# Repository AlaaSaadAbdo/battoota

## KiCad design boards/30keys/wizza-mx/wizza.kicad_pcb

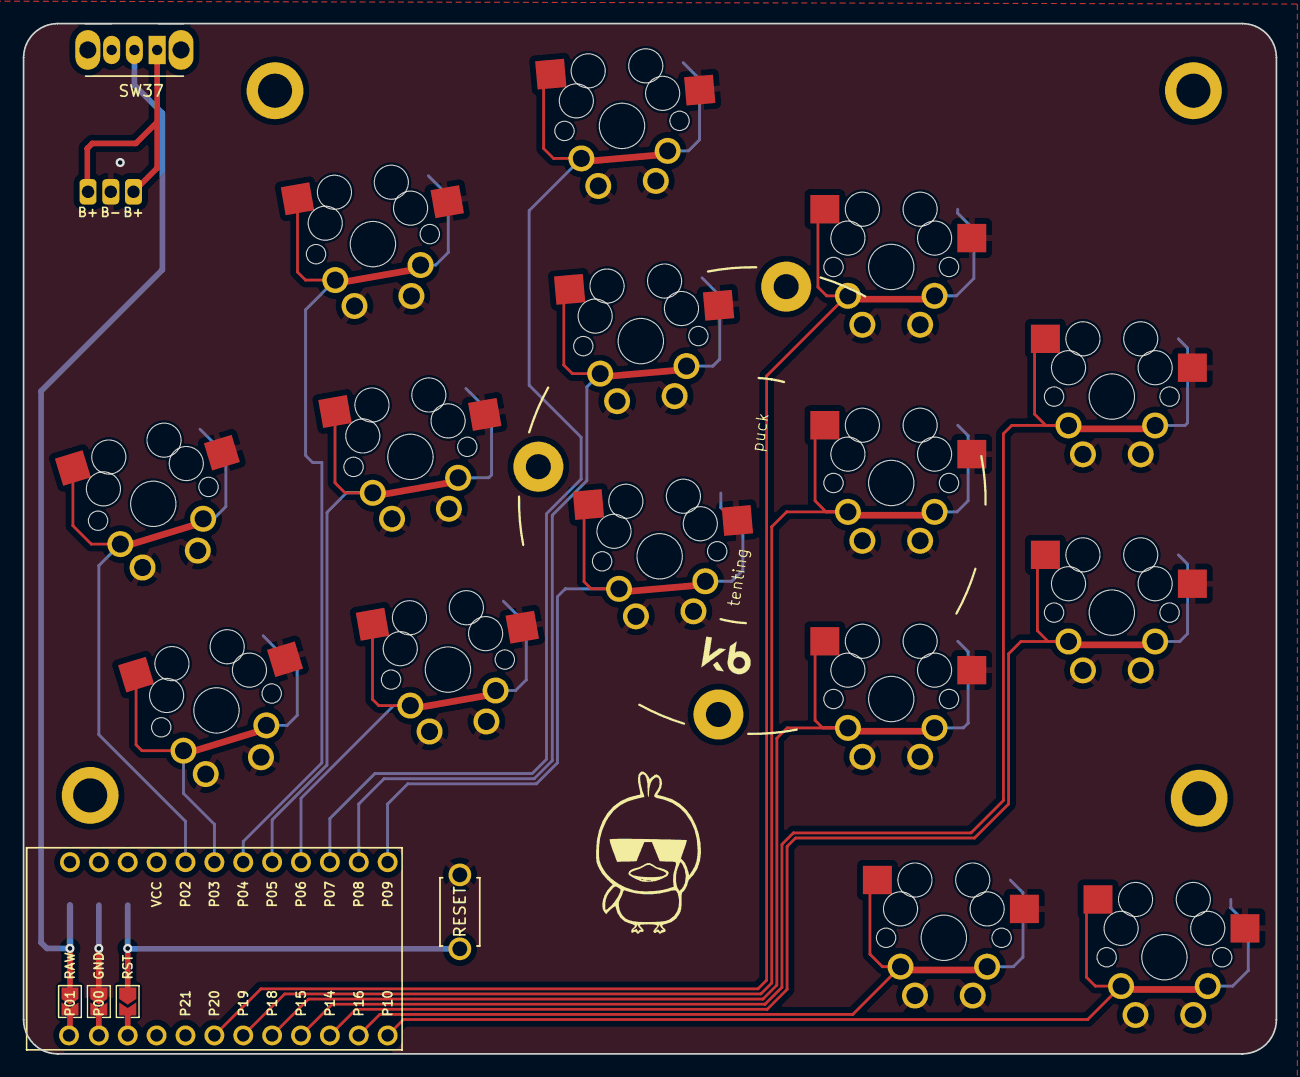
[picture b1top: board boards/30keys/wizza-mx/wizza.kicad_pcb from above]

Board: 2 copper layers, 110.2 x 90.6 mm, 19 parts (0 on the bottom side), 19 nets.

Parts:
B1: ResetSW
MCU1: ProMicro32keys
PAD1: bat
S1, S2, S3, S4, S5, S6, S7, S8, S9, S10, S11, S12, S13, S14, S15: MX-hotswap-reversible
SW37: SW_SPDT; SW_CuK_OS102011MA1QN1_SPDT_Angled

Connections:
GND: B1.2, MCU1.2, PAD1.2, S1.1, S2.1, S3.1, S4.1, S5.1, S6.1, S7.1, S8.1, S9.1, S10.1, S11.1, S12.1, S13.1, S14.1, S15.1
RAW: MCU1.1, SW37.2 (B)
RST: B1.1, MCU1.3
b+: PAD1.1, PAD1.3, SW37.1 (A)
matrix_index_bottom: MCU1.8, S9.2
matrix_index_home: MCU1.7, S10.2
matrix_index_top: MCU1.6, S11.2
matrix_inner_bottom: MCU1.10, S12.2
matrix_inner_home: MCU1.9, S13.2
matrix_middle_bottom: MCU1.24, S6.2
matrix_middle_home: MCU1.23, S7.2
matrix_middle_top: MCU1.22, S8.2
matrix_pinky_home: MCU1.18, S1.2
matrix_pinky_top: MCU1.17, S2.2
matrix_ring_bottom: MCU1.21, S3.2
matrix_ring_home: MCU1.20, S4.2
matrix_ring_top: MCU1.19, S5.2
thumb_reachy: MCU1.12, S15.2
thumb_tucky: MCU1.11, S14.2

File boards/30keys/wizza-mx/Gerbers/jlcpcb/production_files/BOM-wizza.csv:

Comment,Designator,Footprint,LCSC
,S7,MX-hotswap-reversible,
,S8,MX-hotswap-reversible,
,S4,MX-hotswap-reversible,
,MCU1,ProMicro32keys,
,S1,MX-hotswap-reversible,
,S9,MX-hotswap-reversible,
,S12,MX-hotswap-reversible,
,S14,MX-hotswap-reversible,
,S3,MX-hotswap-reversible,
,T2,SPDT_C128955,
,S6,MX-hotswap-reversible,
,S15,MX-hotswap-reversible,
,PAD1,bat,
,B1,ResetSW,
,S11,MX-hotswap-reversible,
,S2,MX-hotswap-reversible,
,S13,MX-hotswap-reversible,
,S5,MX-hotswap-reversible,
,S10,MX-hotswap-reversible,
,T1,SPDT_C128955,

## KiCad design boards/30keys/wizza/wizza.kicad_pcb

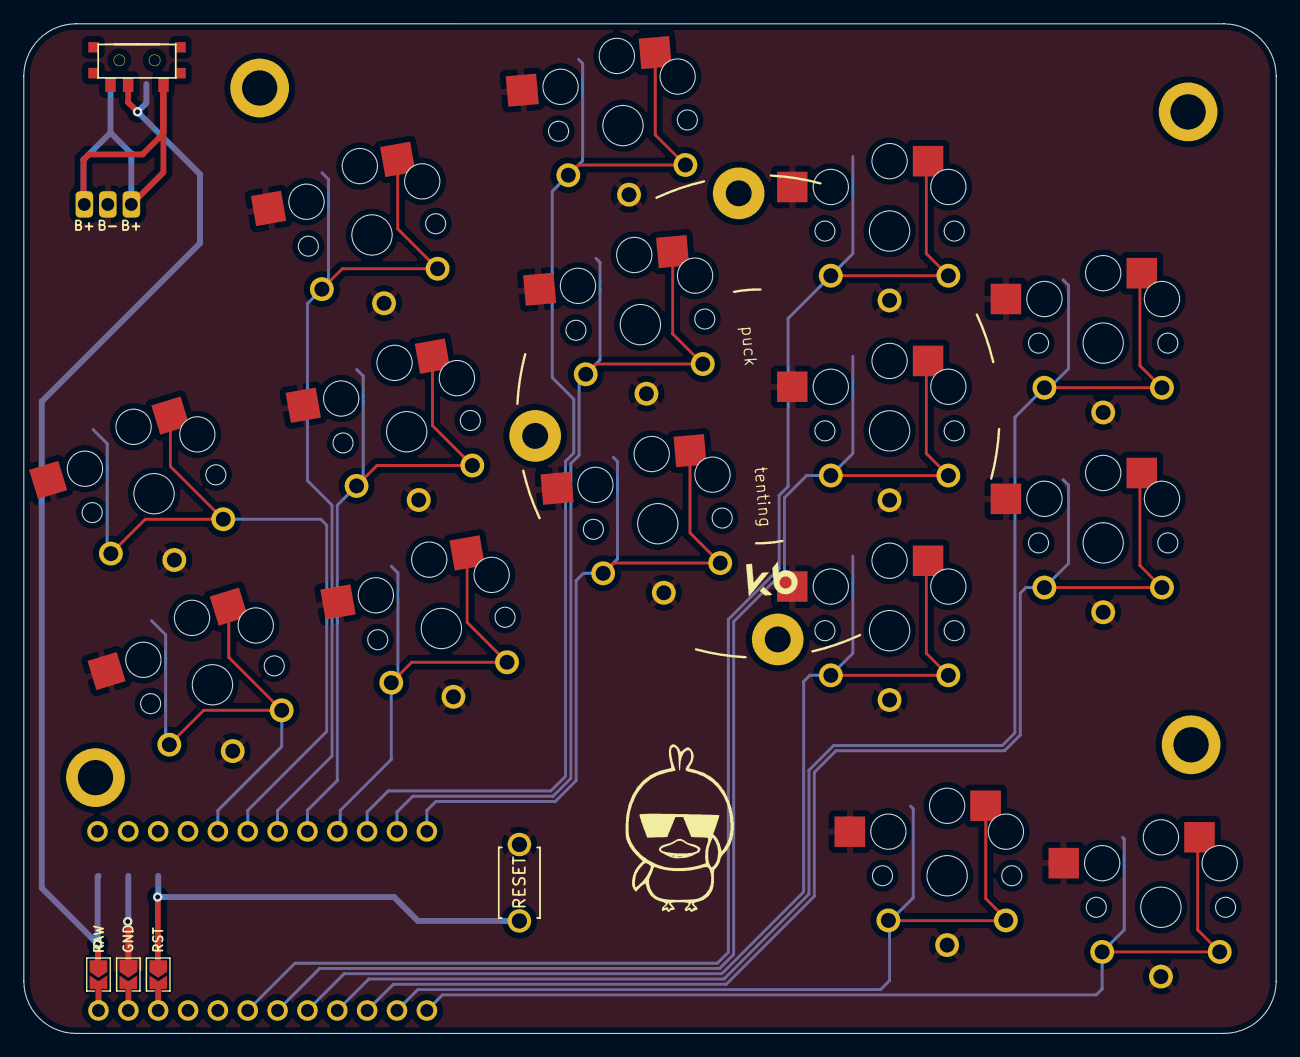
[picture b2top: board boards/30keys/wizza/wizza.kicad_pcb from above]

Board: 2 copper layers, 106.6 x 85.9 mm, 20 parts (1 on the bottom side), 19 nets.

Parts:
B1: ResetSW
MCU1: ProMicro
PAD1: bat
S3, S5, S7, S9, S11, S13, S15, S17, S19, S21, S23, S27, S29, S31, S33: choc_hotswap_key
T1, T2: SPDT_C128955

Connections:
Braw: PAD1.1, PAD1.3, T1.1, T2.1
GND: B1.2, MCU1.2, PAD1.2, S3.2, S5.2, S7.2, S9.2, S11.2, S13.2, S15.2, S17.2, S19.2, S21.2, S23.2, S27.2, S29.2, S31.2, S33.2
P3: MCU1.18, S23.1
P4: MCU1.19, S21.1
P5: MCU1.20, S19.1
P6: MCU1.21, S29.1
P7: MCU1.22, S27.1
P8: MCU1.23, S31.1
P9: MCU1.24, S33.1
P10: MCU1.12, S13.1
P14: MCU1.10, S17.1
P15: MCU1.9, S7.1
P16: MCU1.11, S15.1
P18: MCU1.8, S9.1
P19: MCU1.7, S11.1
P20: MCU1.6, S5.1
P21: MCU1.5, S3.1
RAW: MCU1.1, T1.2, T2.2
RST: B1.1, MCU1.3

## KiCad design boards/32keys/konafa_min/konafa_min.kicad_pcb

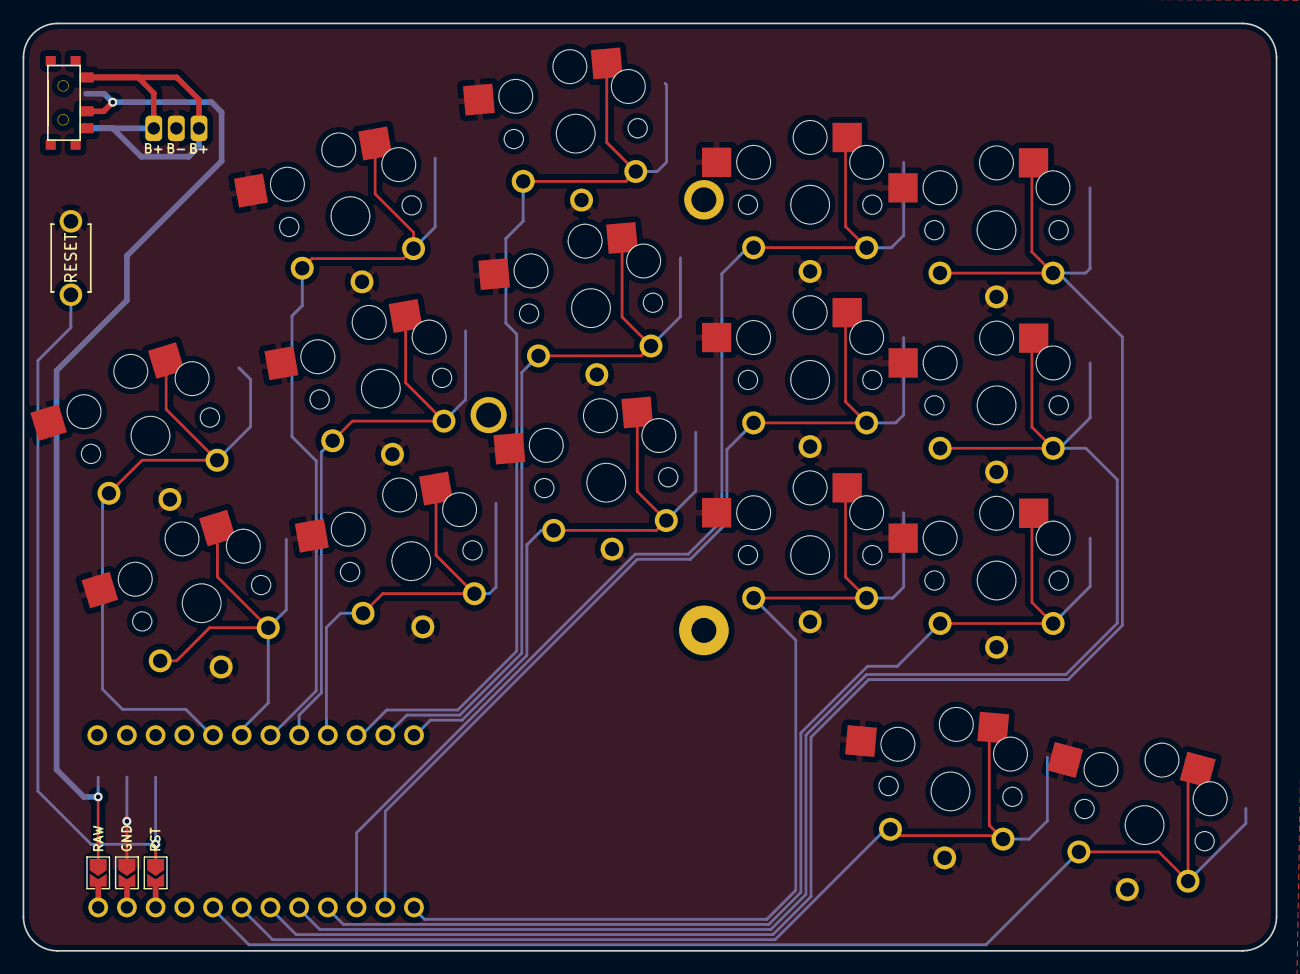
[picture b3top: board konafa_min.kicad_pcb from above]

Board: 2 copper layers, 110.9 x 82.1 mm, 21 parts (1 on the bottom side), 20 nets.

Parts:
B1: ResetSW
MCU1: ProMicro32keys
PAD1: bat
S1, S2, S3, S4, S5, S6, S7, S8, S9, S10, S11, S12, S13, S13#2, S14, S15: key
T1, T2: SPDT_C128955

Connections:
BRAW: PAD1.1, PAD1.3, T1.1, T2.1
GND: B1.1, MCU1.2, PAD1.2, S1.1, S1.2, S2.1, S2.2, S3.1, S3.2, S4.1, S4.2, S5.1, S5.2, S6.1, S6.2, S7.1, S7.2, S8.1, S8.2, S9.1, S9.2, S10.1, S10.2, S11.1, S11.2, S12.1, S12.2, S13.1, S13.2, S13#2.1, S13#2.2, S14.1, S14.2, S15.1, S15.2
P2: MCU1.17, S15.1, S15.2
P3: MCU1.18, S14.1, S14.2
P4: MCU1.19, S13.1, S13.2
P5: MCU1.20, S13#2.1, S13#2.2
P6: MCU1.21, S12.1, S12.2
P7: MCU1.22, S11.1, S11.2
P8: MCU1.23, S10.1, S10.2
P9: MCU1.24, S9.1, S9.2
P10: MCU1.12, S6.1, S6.2
P14: MCU1.10, S8.1, S8.2
P15: MCU1.9, S3.1, S3.2
P16: MCU1.11, S7.1, S7.2
P18: MCU1.8, S4.1, S4.2
P19: MCU1.7, S5.1, S5.2
P20: MCU1.6, S1.1, S1.2
P21: MCU1.5, S2.1, S2.2
RAW: MCU1.1, T1.2, T2.2
RST: B1.2, MCU1.3
